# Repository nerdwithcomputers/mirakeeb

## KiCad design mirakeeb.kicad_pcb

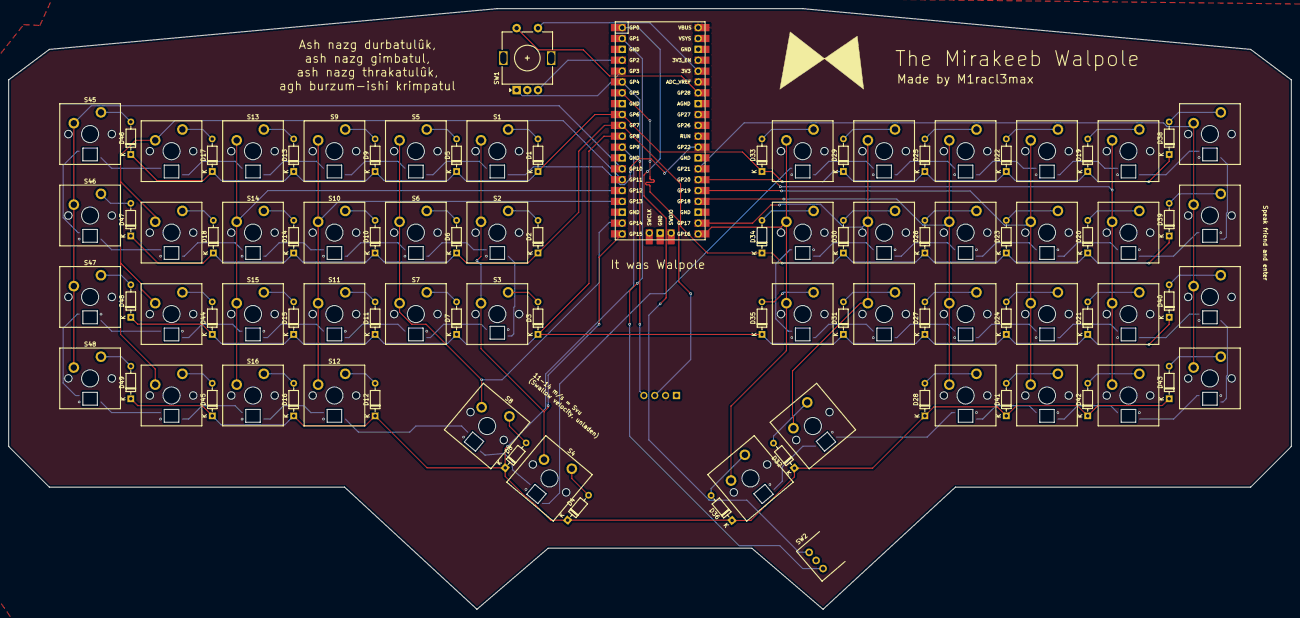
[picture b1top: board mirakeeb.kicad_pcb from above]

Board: 2 copper layers, 300.0 x 140.4 mm, 148 parts (0 on the bottom side), 122 nets.

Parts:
D1, D2, D3, D4, D5, D6, D7, D8, D9, D10, D11, D12, D13, D14, D15, D16, D17, D18, D19, D20, D21, D22, D23, D24, D25, D26, D27, D28, D29, D30, D31, D32, D33, D34, D35, D36, D38, D39, D40, D41, D42, D43, D44, D45, D46, D47, D48, D49: Diode; Diode_DO-35
D50, D51, D52, D53, D54, D55, D56, D57, D58, D59, D60, D61, D62, D63, D64, D65, D66, D67, D68, D69, D70, D71, D72, D73, D74, D75, D76, D77, D78, D79, D80, D81, D82, D83, D84, D85, D86, D87, D88, D89, D90, D91, D92, D93, D94, D95, D96, D97: LED_SK6812MINI
J1: OLED_128x64
S1, S2, S3, S4, S5, S6, S7, S8, S9, S10, S11, S12, S13, S14, S15, S16, S17, S18, S19, S20, S21, S22, S23, S24, S25, S26, S27, S28, S29, S30, S31, S32, S33, S34, S35, S36, S37, S38, S39, S40, S41, S42, S43, S44, S45, S46, S47, S48: Keyswitch; MX_PCB_1.00u
SW1: RotaryEncoder_Switch; RotaryEncoder_Alps_EC11E-Switch_Vertical_H20mm
SW2: RotaryEncoder; RotaryEncoder_Bourns_Horizontal_PEC09-2xxxF-Nxxxx
U1: Raspberry_Pi_Pico

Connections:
+3.3V: SW1.S1, U1.36 (3V3)
+5V: D50.4 (VDD), D51.4 (VDD), D52.4 (VDD), D53.4 (VDD), D54.4 (VDD), D55.4 (VDD), D56.4 (VDD), D57.4 (VDD), D58.4 (VDD), D59.4 (VDD), D60.4 (VDD), D61.4 (VDD), D62.4 (VDD), D63.4 (VDD), D64.4 (VDD), D65.4 (VDD), D66.4 (VDD), D67.4 (VDD), D68.4 (VDD), D69.4 (VDD), D70.4 (VDD), D71.4 (VDD), D72.4 (VDD), D73.4 (VDD), D74.4 (VDD), D75.4 (VDD), D76.4 (VDD), D77.4 (VDD), D78.4 (VDD), D79.4 (VDD), D80.4 (VDD), D81.4 (VDD), D82.4 (VDD), D83.4 (VDD), D84.4 (VDD), D85.4 (VDD), D86.4 (VDD), D87.4 (VDD), D88.4 (VDD), D89.4 (VDD), D90.4 (VDD), D91.4 (VDD), D92.4 (VDD), D93.4 (VDD), D94.4 (VDD), D95.4 (VDD), D96.4 (VDD), D97.4 (VDD), J1.2 (VCC), U1.40 (VBUS)
C0: S45.1, S46.1, S47.1, S48.1, U1.14 (GPIO10)
C1: S17.1, S18.1, S43.1, S44.1, U1.15 (GPIO11)
C2: S13.1, S14.1, S15.1, S16.1, U1.16 (GPIO12)
C3: S9.1, S10.1, S11.1, S12.1, U1.17 (GPIO13)
C4: S5.1, S6.1, S7.1, S8.1, U1.19 (GPIO14)
C5: S1.1, S2.1, S3.1, S4.1, U1.20 (GPIO15)
C6: S33.1, S34.1, S35.1, S36.1, U1.21 (GPIO16)
C7: S29.1, S30.1, S31.1, S32.1, U1.22 (GPIO17)
C8: S25.1, S26.1, S27.1, S28.1, U1.24 (GPIO18)
C9: S22.1, S23.1, S24.1, S40.1, U1.25 (GPIO19)
GND: D50.2 (VSS), D51.2 (VSS), D52.2 (VSS), D53.2 (VSS), D54.2 (VSS), D55.2 (VSS), D56.2 (VSS), D57.2 (VSS), D58.2 (VSS), D59.2 (VSS), D60.2 (VSS), D61.2 (VSS), D62.2 (VSS), D63.2 (VSS), D64.2 (VSS), D65.2 (VSS), D66.2 (VSS), D67.2 (VSS), D68.2 (VSS), D69.2 (VSS), D70.2 (VSS), D71.2 (VSS), D72.2 (VSS), D73.2 (VSS), D74.2 (VSS), D75.2 (VSS), D76.2 (VSS), D77.2 (VSS), D78.2 (VSS), D79.2 (VSS), D80.2 (VSS), D81.2 (VSS), D82.2 (VSS), D83.2 (VSS), D84.2 (VSS), D85.2 (VSS), D86.2 (VSS), D87.2 (VSS), D88.2 (VSS), D89.2 (VSS), D90.2 (VSS), D91.2 (VSS), D92.2 (VSS), D93.2 (VSS), D94.2 (VSS), D95.2 (VSS), D96.2 (VSS), D97.2 (VSS), J1.1 (GND), SW1.C, SW2.C, U1.3 (GND), U1.8 (GND), U1.13 (GND), U1.18 (GND), U1.23 (GND), U1.28 (GND), U1.38 (GND)
unnamed: D1.2 (A), S1.2
unnamed: D2.2 (A), S2.2
unnamed: D3.2 (A), S3.2
unnamed: D4.2 (A), S4.2
unnamed: D5.2 (A), S5.2
unnamed: D6.2 (A), S6.2
unnamed: D7.2 (A), S7.2
unnamed: D8.2 (A), S8.2
unnamed: D9.2 (A), S9.2
unnamed: D10.2 (A), S10.2
unnamed: D11.2 (A), S11.2
unnamed: D12.2 (A), S12.2
unnamed: D13.2 (A), S13.2
unnamed: D14.2 (A), S14.2
unnamed: D15.2 (A), S15.2
unnamed: D16.2 (A), S16.2
unnamed: D17.2 (A), S17.2
unnamed: D18.2 (A), S18.2
unnamed: D19.2 (A), S19.2
unnamed: D20.2 (A), S20.2
unnamed: D21.2 (A), S21.2
unnamed: D22.2 (A), S22.2
unnamed: D23.2 (A), S23.2
unnamed: D24.2 (A), S24.2
unnamed: D25.2 (A), S25.2
unnamed: D26.2 (A), S26.2
unnamed: D27.2 (A), S27.2
unnamed: D28.2 (A), S28.2
unnamed: D29.2 (A), S29.2
unnamed: D30.2 (A), S30.2
unnamed: D31.2 (A), S31.2
unnamed: D32.2 (A), S32.2
unnamed: D33.2 (A), S33.2
unnamed: D34.2 (A), S34.2
unnamed: D35.2 (A), S35.2
unnamed: D36.2 (A), S36.2
unnamed: D38.2 (A), S37.2
unnamed: D39.2 (A), S38.2
unnamed: D40.2 (A), S39.2
unnamed: D41.2 (A), S40.2
unnamed: D42.2 (A), S41.2
unnamed: D43.2 (A), S42.2
unnamed: D44.2 (A), S43.2
unnamed: D45.2 (A), S44.2
unnamed: D46.2 (A), S45.2
unnamed: D47.2 (A), S46.2
unnamed: D48.2 (A), S47.2
unnamed: D49.2 (A), S48.2
unnamed: D50.1 (DOUT), D51.3 (DIN)
unnamed: D51.1 (DOUT), D52.3 (DIN)
unnamed: D52.1 (DOUT), D53.3 (DIN)
unnamed: D53.1 (DOUT), D54.3 (DIN)
unnamed: D54.1 (DOUT), D55.3 (DIN)
unnamed: D55.1 (DOUT), D62.3 (DIN)
unnamed: D56.3 (DIN), D79.1 (DOUT)
unnamed: D56.1 (DOUT), D60.3 (DIN)
unnamed: D57.3 (DIN), D61.1 (DOUT)
unnamed: D57.1 (DOUT), D58.3 (DIN)
unnamed: D58.1 (DOUT), D80.3 (DIN)
unnamed: D59.3 (DIN), D81.1 (DOUT)
unnamed: D60.1 (DOUT), D82.3 (DIN)
unnamed: D61.3 (DIN), D83.1 (DOUT)
unnamed: D62.1 (DOUT), D63.3 (DIN)
unnamed: D63.1 (DOUT), D64.3 (DIN)
unnamed: D64.1 (DOUT), D65.3 (DIN)
unnamed: D65.1 (DOUT), D66.3 (DIN)
unnamed: D66.1 (DOUT), D67.3 (DIN)
unnamed: D67.1 (DOUT), D68.3 (DIN)
unnamed: D68.1 (DOUT), D70.3 (DIN)
unnamed: D69.3 (DIN), D78.1 (DOUT)
unnamed: D69.1 (DOUT), D71.3 (DIN)
unnamed: D70.1 (DOUT), D72.3 (DIN)
unnamed: D71.1 (DOUT), D73.3 (DIN)
unnamed: D72.1 (DOUT), D74.3 (DIN)
unnamed: D73.1 (DOUT), D75.3 (DIN)
unnamed: D74.1 (DOUT), D76.3 (DIN)
unnamed: D75.1 (DOUT), D77.3 (DIN)
unnamed: D76.1 (DOUT), D78.3 (DIN)
unnamed: D77.1 (DOUT), D79.3 (DIN)
unnamed: D80.1 (DOUT), D84.3 (DIN)
unnamed: D81.3 (DIN), D85.1 (DOUT)
unnamed: D82.1 (DOUT), D86.3 (DIN)
unnamed: D83.3 (DIN), D87.1 (DOUT)
unnamed: D84.1 (DOUT), D88.3 (DIN)
unnamed: D85.3 (DIN), D89.1 (DOUT)
unnamed: D86.1 (DOUT), D90.3 (DIN)
unnamed: D87.3 (DIN), D91.1 (DOUT)
unnamed: D88.1 (DOUT), D92.3 (DIN)
unnamed: D89.3 (DIN), D93.1 (DOUT)
unnamed: D90.1 (DOUT), D94.3 (DIN)
unnamed: D91.3 (DIN), D95.1 (DOUT)
unnamed: D92.1 (DOUT), D96.3 (DIN)
unnamed: D93.3 (DIN), D97.1 (DOUT)
unnamed: D94.1 (DOUT), D95.3 (DIN)
unnamed: D96.1 (DOUT), D97.3 (DIN)
unnamed: SW2.B, U1.1 (GPIO0)
unnamed: SW2.A, U1.2 (GPIO1)
unnamed: SW1.B, U1.4 (GPIO2)
unnamed: SW1.A, U1.5 (GPIO3)
unnamed: SW1.S2, U1.34 (GPIO28_ADC2)
R0: D1.1 (K), D5.1 (K), D9.1 (K), D13.1 (K), D17.1 (K), D19.1 (K), D22.1 (K), D25.1 (K), D29.1 (K), D33.1 (K), D38.1 (K), D46.1 (K), U1.9 (GPIO6)
R1: D2.1 (K), D6.1 (K), D10.1 (K), D14.1 (K), D18.1 (K), D20.1 (K), D23.1 (K), D26.1 (K), D30.1 (K), D34.1 (K), D39.1 (K), D47.1 (K), U1.10 (GPIO7)
R2: D3.1 (K), D7.1 (K), D11.1 (K), D15.1 (K), D21.1 (K), D24.1 (K), D27.1 (K), D31.1 (K), D35.1 (K), D40.1 (K), D44.1 (K), D48.1 (K), U1.11 (GPIO8)
R3: D4.1 (K), D8.1 (K), D12.1 (K), D16.1 (K), D28.1 (K), D32.1 (K), D36.1 (K), D41.1 (K), D42.1 (K), D43.1 (K), D45.1 (K), D49.1 (K), U1.12 (GPIO9)
c10: S19.1, S20.1, S21.1, S41.1, U1.26 (GPIO20)
c11: S37.1, S38.1, S39.1, S42.1, U1.27 (GPIO21)
ledhalf0: D50.3 (DIN), U1.29 (GPIO22)
scl: J1.3 (SCL), U1.7 (GPIO5)
sda: J1.4 (SDA), U1.6 (GPIO4)

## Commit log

2025-02-15 init
2025-02-16 more stuff
2025-02-16 asdf
2025-02-17 wiring is hard
2025-02-17 ping
2025-02-17 pong
2025-03-14 pretty much final design, just need graphics
2025-03-14 graphics
